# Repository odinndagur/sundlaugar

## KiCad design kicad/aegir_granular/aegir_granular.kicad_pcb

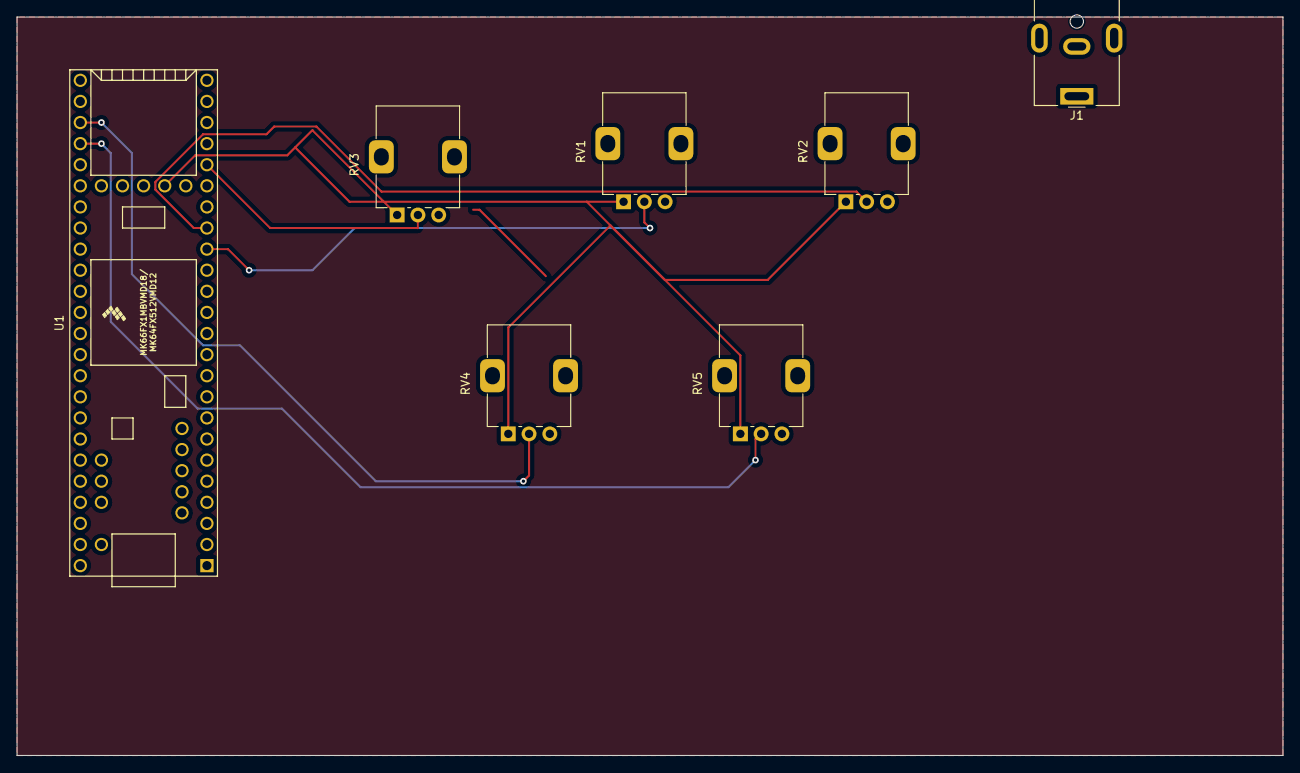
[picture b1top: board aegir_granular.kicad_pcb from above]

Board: 2 copper layers, 152.4 x 88.9 mm, 7 parts (0 on the bottom side), 6 nets.

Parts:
J1: Barrel_Jack; BarrelJack_CUI_PJ-063AH_Horizontal
RV1, RV2, RV3, RV4, RV5: R_Potentiometer; Potentiometer_Alps_RK09K_Single_Vertical
U1: Teensy3.6; Teensy35_36

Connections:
/density_pot: RV3.2, U1.20 (28)
/grain_size_pot: RV1.2, U1.16 (24)
/spread_pot: RV2.2, U1.17 (25)
GND: J1.2, RV1.3, RV2.3, RV3.3, RV4.3, RV5.3, U1.1 (GND)
VCC: J1.1, U1.53 (VIN)
teensy_3v3: RV1.1, RV2.1, RV3.1, RV4.1, RV5.1, U1.26 (3V3)

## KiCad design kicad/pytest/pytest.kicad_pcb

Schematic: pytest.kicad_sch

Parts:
BT1: 9v; BatteryHolder_Keystone_2462_2xAA
D1: white led; LED_2512_6332Metric_Pad1.52x3.35mm_HandSolder
D2: blue led; LED_2512_6332Metric_Pad1.52x3.35mm_HandSolder
D3: red led; LED_2512_6332Metric_Pad1.52x3.35mm_HandSolder
SW1: switch1; SW_SPST_B3S-1000
SW2: switch2; SW_SPST_B3S-1000
SW3: switch3; SW_SPST_B3S-1000

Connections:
GNDPWR: BT1.2 (-), D1.1 (K), D2.1 (K), D3.1 (K)
unnamed: BT1.1 (+), SW1.1, SW2.1, SW3.1
unnamed: D1.2 (A), SW1.2
unnamed: D2.2 (A), SW2.2
unnamed: D3.2 (A), SW3.2

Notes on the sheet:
(footprint "Graphics" (layer "F.SilkS") (at 0 0) (attr board_only exclude_from_pos_files exclude_from_bom) (tstamp "ce9799be-2456-11ed-907b-acde48001122") (tedit "ce9799dc-2456-11ed-907b-acde48001122") (fp_poly (pts (xy 0.876140 -1.204980) (xy 1.287760 -1.204960) (xy 1.680640 -1.204920) (xy 2.05520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

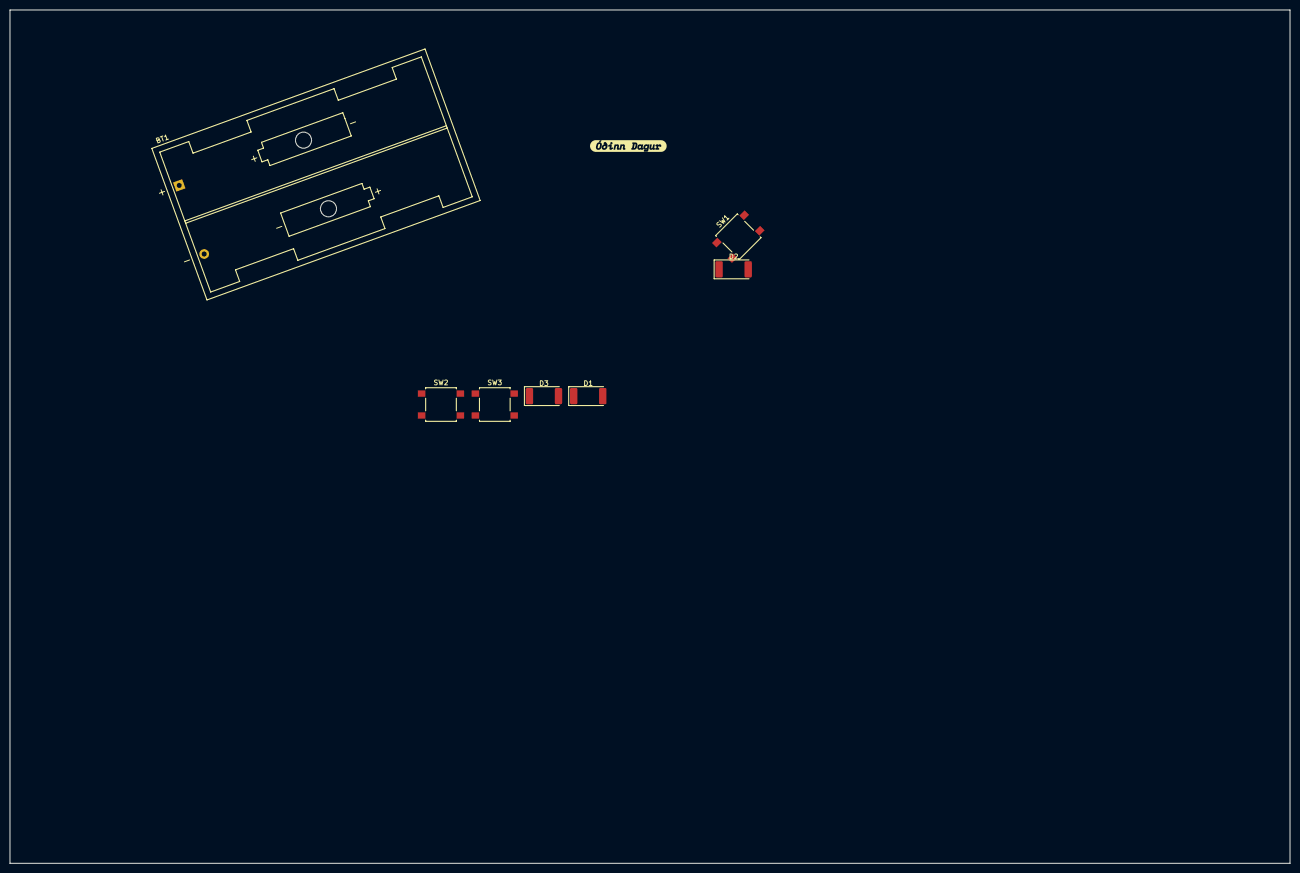
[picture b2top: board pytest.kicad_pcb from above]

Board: 2 copper layers, 262.9 x 175.3 mm, 7 parts (0 on the bottom side), 5 nets, no tracks yet.

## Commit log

2022-02-10 initial
2022-02-19 alltadgerast
2022-02-20 nice
2024-07-01 rest
